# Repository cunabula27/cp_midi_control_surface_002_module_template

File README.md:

# CP Midi Control Surface 002 Module Template
 KiCad template for designing extension modules for the [CP Midi Control Surface 002](https://github.com/cunabula27/cp_midi_control_surface_002).

## Directions
Clone the repository into your local KiCad template folder which you can find via the menu in KiCad&rsquo;s Project page under __Preferences > Configure Paths__ in the line KICAD_USER_TEMPLATE_DIR.

To start a new project using the template either click on the _Create a new project from template_ icon (the second in the row) or use the __File__ menu. If everything has gone correctly you will find the template under the _User Templates_ tab in the pop up window.

## What&rsquo;s included

The template contains a schematic with several hierarchical sheets containing the 16 sockets and four multiplexers that it&rsquo;s possible to connect to the main board. It should all be fairly self-explanatory. The top page contains the left-hand multiplexer and all the sockets that connect to anything other than GND. There are three sub pages for each of the other multiplexers and one for the GND sockets. All the socket pins are either connected to the correct multiplexer or have net labels attached that match the Arduino pin they ultimately connect to. I've also marked which pins are digital and which are analogue.

There's also an initial PCB layout to get you started. All the sockets are in the correct place to line up with the rails and headers below and the multiplexers are placed in the centre of each section that they correspond to. On the Eco1.User layer I've marked the maximum size that a board can be and also the widths of the original boards for the project if you're also using some of them. I&rsquo;ve also ghosted in the pins from the rails for reference. Feel free to delete them if they&rsquo;re confusing.

## Available connections

The full size board makes available 71 analogue connections and 24 digital connections - which gives a lot of scope to play with. The _[OpenDeck wiki](https://github.com/paradajz/OpenDeck/wiki/Connections)_ lists all the pinouts for possible components and explains how to connect buttons to analogue pins (add a 10k resistor between the button and ground). For the digital pins (encoders/buttons) the net labels in the schematic correspond to the Arduino Mega2560 pins in the wiki.

## Notes

Delete the bits you don't need (__with a couple of notes of caution__). The schematic and layout contain everything it's possible to connect to the main board, if you're only making a smaller board, get rid of the rest. VCC is connected via the main board, you don't need separate power.

The system is designed to be connected together with headers/sockets* and one of the GND ones at the bottom of the board (J9, J11, J13, J15) must be used as they connect sub-board GND to the main board. You can shrink them to less pins if you like but they should be there in some form. Also make sure you have a GND plane on both the top and bottom of the final board.

If you&rsquo;re using J10 and/or J12 they have connections you may not need. It's fine to change them to smaller or separate components for the connections you&rsquo;re using but make sure the replacements are in the right place. For instance, if you only want the multiplexer bit of J12 you can safely swap it for a 2x3 socket but make sure pin 1 is still in the same place on the board or it won&rsquo;t work.

And finally, I'd suggest leaving 100 mils between boards to make it slightly easier to fit them in or swap them around.

*This is the first electronics project I've undertaken and I had a devil of a job working out how to match the heights of different controls &ndash; header/socket combinations of different lengths fit the bill and it seemed like a good idea to use them throughout, as it also cut out the need for ribbon cable or other ways to connect everything together. If I was doing this again, I'd mainly use standoffs and just use headers and socets for what they're designed for. It&rsquo;s all well and good designing something sturdy and modular, but changing the modules would be a lot easier with standoffs doing most of the holding together. Sorry about that.

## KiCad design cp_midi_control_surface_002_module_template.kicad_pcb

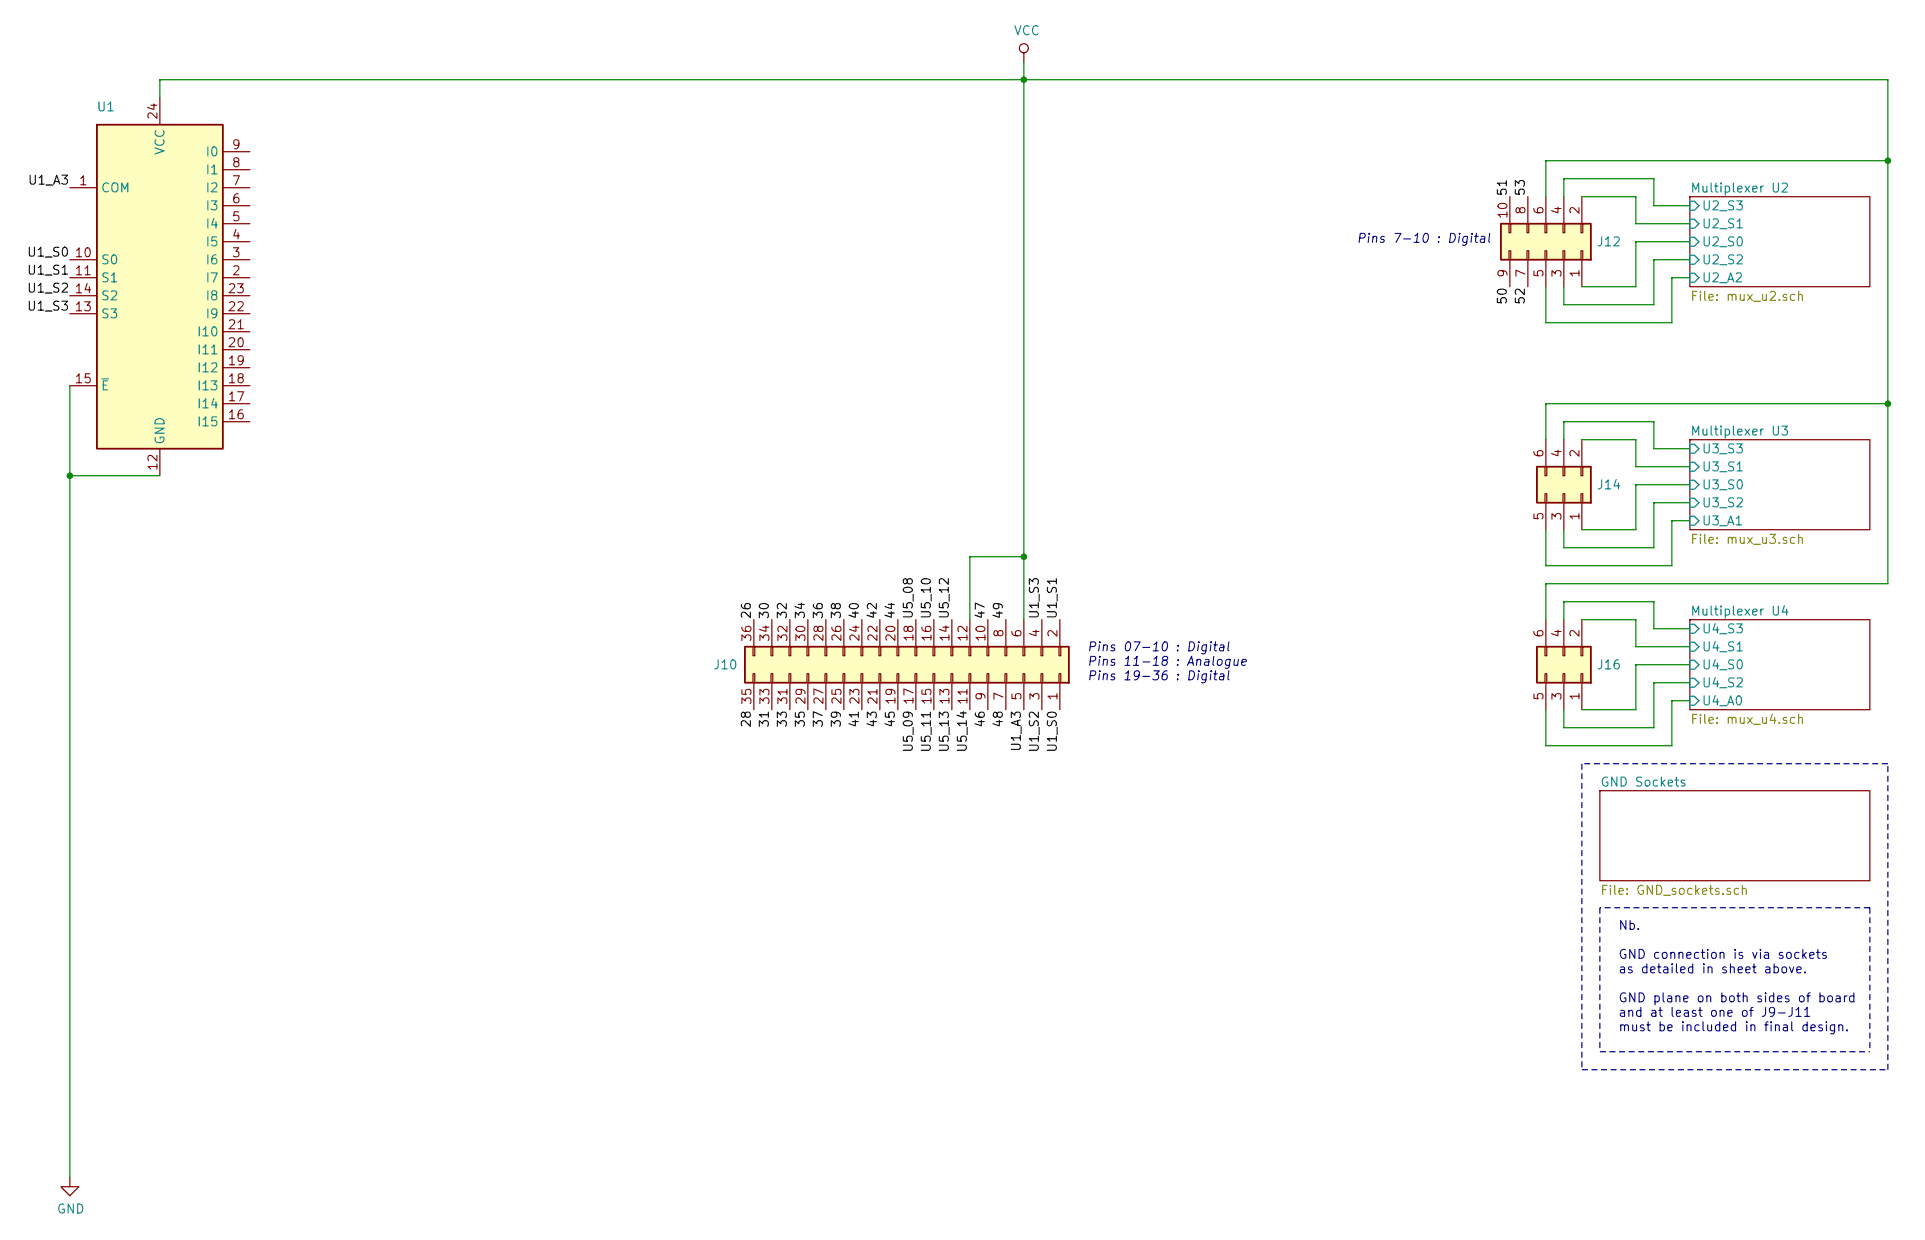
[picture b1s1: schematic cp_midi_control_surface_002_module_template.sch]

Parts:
J10: Conn_02x18_Odd_Even; PinHeader_2x18_P2.54mm_Vertical
J12: Conn_02x05_Odd_Even; PinHeader_2x05_P2.54mm_Vertical
J14: Conn_02x03_Counter_Clockwise; PinHeader_2x03_P2.54mm_Vertical
J16: Conn_02x03_Odd_Even; PinHeader_2x03_P2.54mm_Vertical
U1: CD74HC4067M; SOIC-24W_7.5x15.4mm_P1.27mm

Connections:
/26: J10.36
/28: J10.35
/30: J10.34
/31: J10.33
/32: J10.32
/33: J10.31
/34: J10.30
/35: J10.29
/36: J10.28
/37: J10.27
/38: J10.26
/39: J10.25
/40: J10.24
/41: J10.23
/42: J10.22
/43: J10.21
/44: J10.20
/45: J10.19
/46: J10.9
/47: J10.10
/48: J10.7
/49: J10.8
/50: J12.9
/51: J12.10
/52: J12.7
/53: J12.8
/Multiplexer A0/U4_A0: J16.5; also elsewhere on the board
/Multiplexer A0/U4_S0: J16.1; also elsewhere on the board
/Multiplexer A0/U4_S1: J16.2; also elsewhere on the board
/Multiplexer A0/U4_S2: J16.3; also elsewhere on the board
/Multiplexer A0/U4_S3: J16.4; also elsewhere on the board
/Multiplexer A1/U3_A1: J14.5; also elsewhere on the board
/Multiplexer A1/U3_S0: J14.1; also elsewhere on the board
/Multiplexer A1/U3_S1: J14.2; also elsewhere on the board
/Multiplexer A1/U3_S2: J14.3; also elsewhere on the board
/Multiplexer A1/U3_S3: J14.4; also elsewhere on the board
/Multiplexer A2/U2_A2: J12.5; also elsewhere on the board
/Multiplexer A2/U2_S0: J12.1; also elsewhere on the board
/Multiplexer A2/U2_S1: J12.2; also elsewhere on the board
/Multiplexer A2/U2_S2: J12.3; also elsewhere on the board
/Multiplexer A2/U2_S3: J12.4; also elsewhere on the board
/U1_A3: J10.5, U1.1 (COM)
/U1_S0: J10.1, U1.10 (S0)
/U1_S1: J10.2, U1.11 (S1)
/U1_S2: J10.3, U1.14 (S2)
/U1_S3: J10.4, U1.13 (S3)
/U5_08: J10.18
/U5_09: J10.17
/U5_10: J10.16
/U5_11: J10.15
/U5_12: J10.14
/U5_13: J10.13
/U5_14: J10.11
GND: U1.12 (GND), U1.15 (~E); also elsewhere on the board
VCC: J10.6, J10.12, J12.6, J14.6, J16.6, U1.24 (VCC); also elsewhere on the board

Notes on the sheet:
Pins 07-10 : Digital Pins 11-18 : Analogue Pins 19-36 : Digital
Pins 7-10 : Digital
Nb. GND connection is via sockets as detailed in sheet above. GND plane on both sides of board and at least one of J9-J11 must be included in final design.

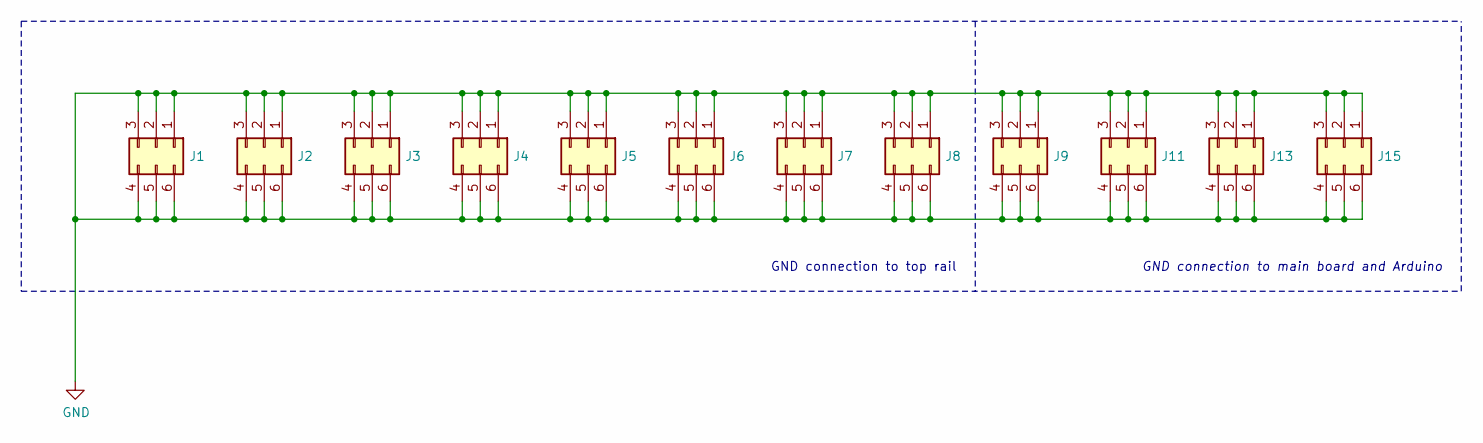
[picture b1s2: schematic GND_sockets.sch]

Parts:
J1, J2, J3, J4, J5, J6, J7, J8, J9, J11, J13, J15: Conn_02x03_Counter_Clockwise; PinHeader_2x03_P2.54mm_Vertical

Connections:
GND: J1.1, J1.2, J1.3, J1.4, J1.5, J1.6, J2.1, J2.2, J2.3, J2.4, J2.5, J2.6, J3.1, J3.2, J3.3, J3.4, J3.5, J3.6, J4.1, J4.2, J4.3, J4.4, J4.5, J4.6, J5.1, J5.2, J5.3, J5.4, J5.5, J5.6, J6.1, J6.2, J6.3, J6.4, J6.5, J6.6, J7.1, J7.2, J7.3, J7.4, J7.5, J7.6, J8.1, J8.2, J8.3, J8.4, J8.5, J8.6, J9.1, J9.2, J9.3, J9.4, J9.5, J9.6, J11.1, J11.2, J11.3, J11.4, J11.5, J11.6, J13.1, J13.2, J13.3, J13.4, J13.5, J13.6, J15.1, J15.2, J15.3, J15.4, J15.5, J15.6; also elsewhere on the board

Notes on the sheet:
GND connection to main board and Arduino
GND connection to top rail

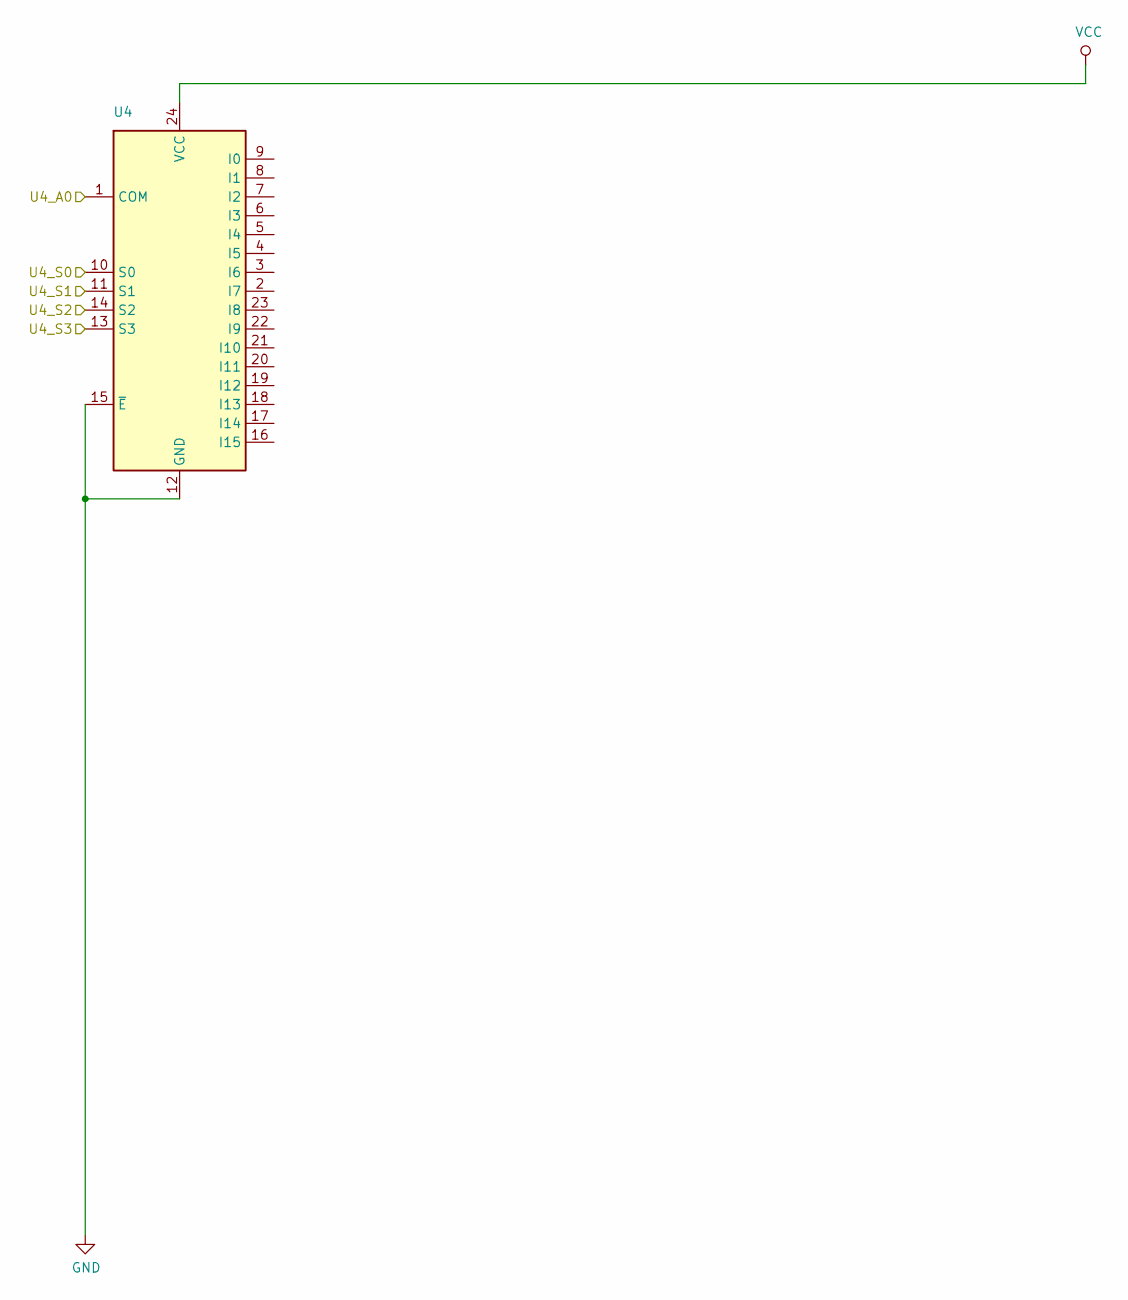
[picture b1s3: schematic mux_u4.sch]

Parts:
U4: CD74HC4067M; SOIC-24W_7.5x15.4mm_P1.27mm

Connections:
/Multiplexer A0/U4_A0: U4.1 (COM); also elsewhere on the board
/Multiplexer A0/U4_S0: U4.10 (S0); also elsewhere on the board
/Multiplexer A0/U4_S1: U4.11 (S1); also elsewhere on the board
/Multiplexer A0/U4_S2: U4.14 (S2); also elsewhere on the board
/Multiplexer A0/U4_S3: U4.13 (S3); also elsewhere on the board
GND: U4.12 (GND), U4.15 (~E); also elsewhere on the board
VCC: U4.24 (VCC); also elsewhere on the board

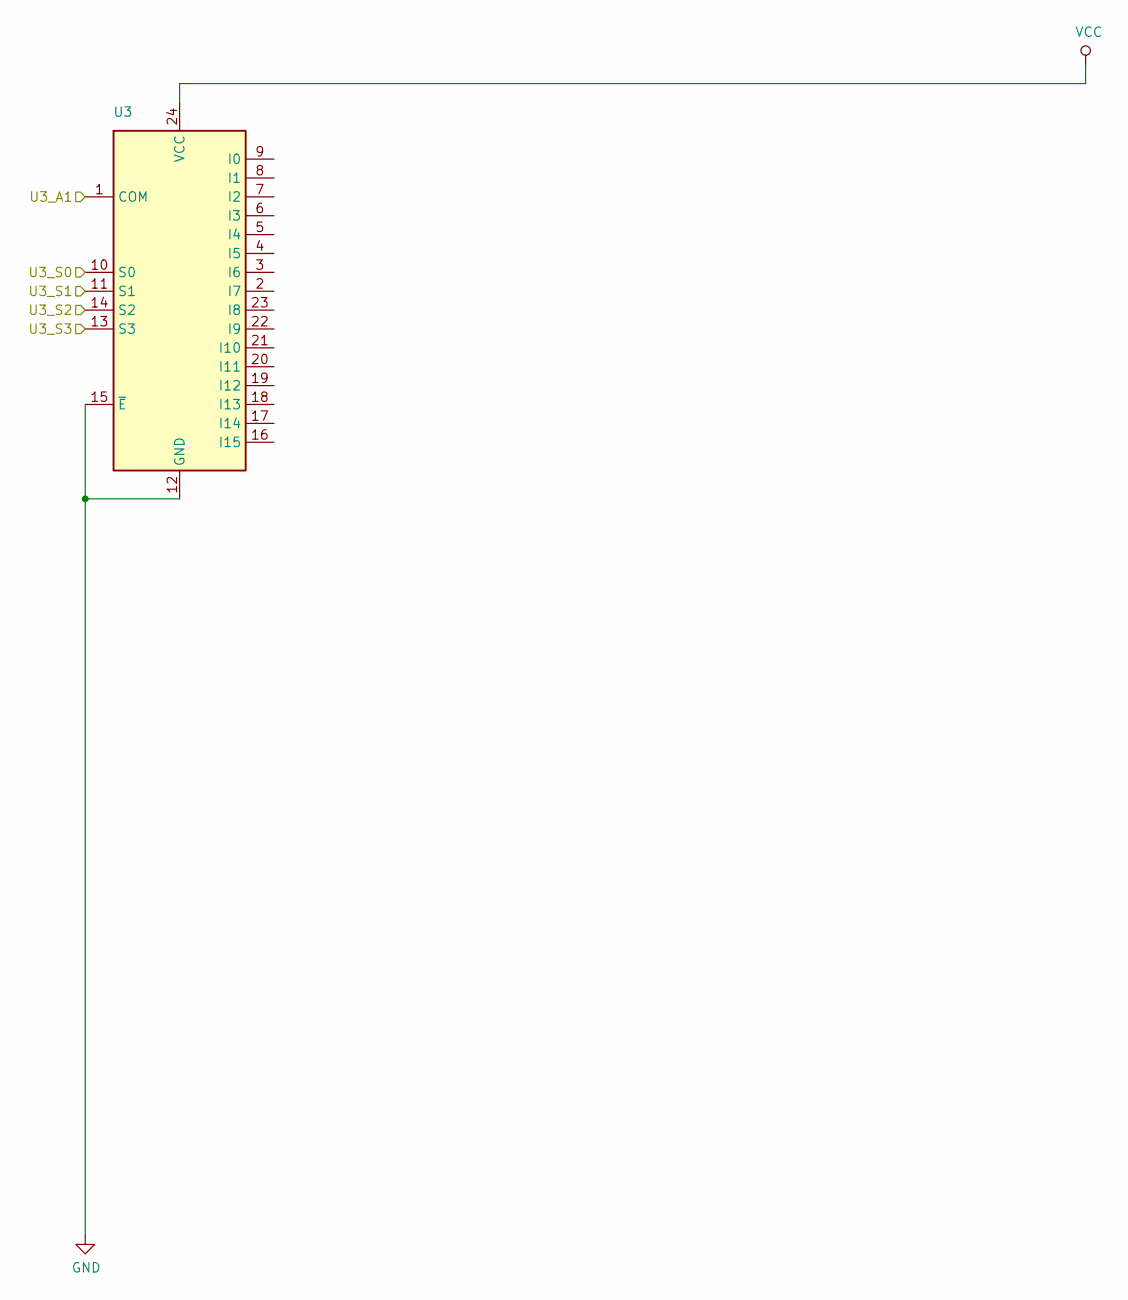
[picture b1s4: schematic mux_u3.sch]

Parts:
U3: CD74HC4067M; SOIC-24W_7.5x15.4mm_P1.27mm

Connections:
/Multiplexer A1/U3_A1: U3.1 (COM); also elsewhere on the board
/Multiplexer A1/U3_S0: U3.10 (S0); also elsewhere on the board
/Multiplexer A1/U3_S1: U3.11 (S1); also elsewhere on the board
/Multiplexer A1/U3_S2: U3.14 (S2); also elsewhere on the board
/Multiplexer A1/U3_S3: U3.13 (S3); also elsewhere on the board
GND: U3.12 (GND), U3.15 (~E); also elsewhere on the board
VCC: U3.24 (VCC); also elsewhere on the board

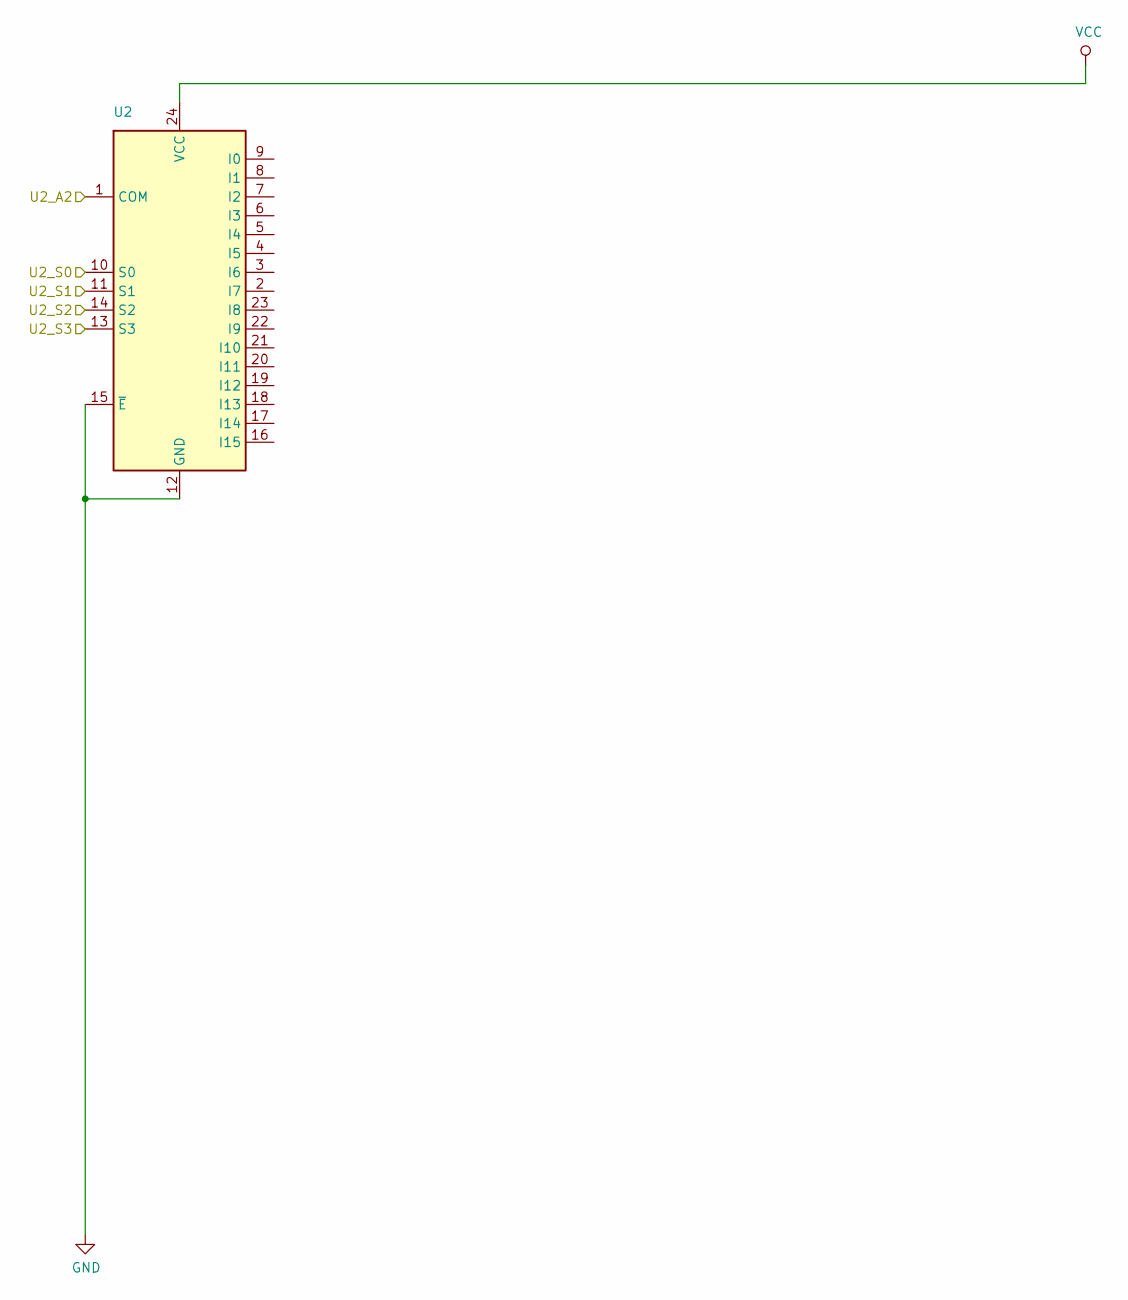
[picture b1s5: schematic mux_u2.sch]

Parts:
U2: CD74HC4067M; SOIC-24W_7.5x15.4mm_P1.27mm

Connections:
/Multiplexer A2/U2_A2: U2.1 (COM); also elsewhere on the board
/Multiplexer A2/U2_S0: U2.10 (S0); also elsewhere on the board
/Multiplexer A2/U2_S1: U2.11 (S1); also elsewhere on the board
/Multiplexer A2/U2_S2: U2.14 (S2); also elsewhere on the board
/Multiplexer A2/U2_S3: U2.13 (S3); also elsewhere on the board
GND: U2.12 (GND), U2.15 (~E); also elsewhere on the board
VCC: U2.24 (VCC); also elsewhere on the board

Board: 2 copper layers, 20 parts (20 on the bottom side), 22 nets, no tracks yet.

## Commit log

2019-10-10 Added opening waffle.
2019-10-10 Cleaned up text of Readme
2019-11-03 Update cp_midi_control_surface_002_module_template.kicad_pcb
    Test measuring for 84 HP layout
